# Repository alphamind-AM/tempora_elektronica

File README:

author: Alphamind
year: 2024
dyslexia: yes

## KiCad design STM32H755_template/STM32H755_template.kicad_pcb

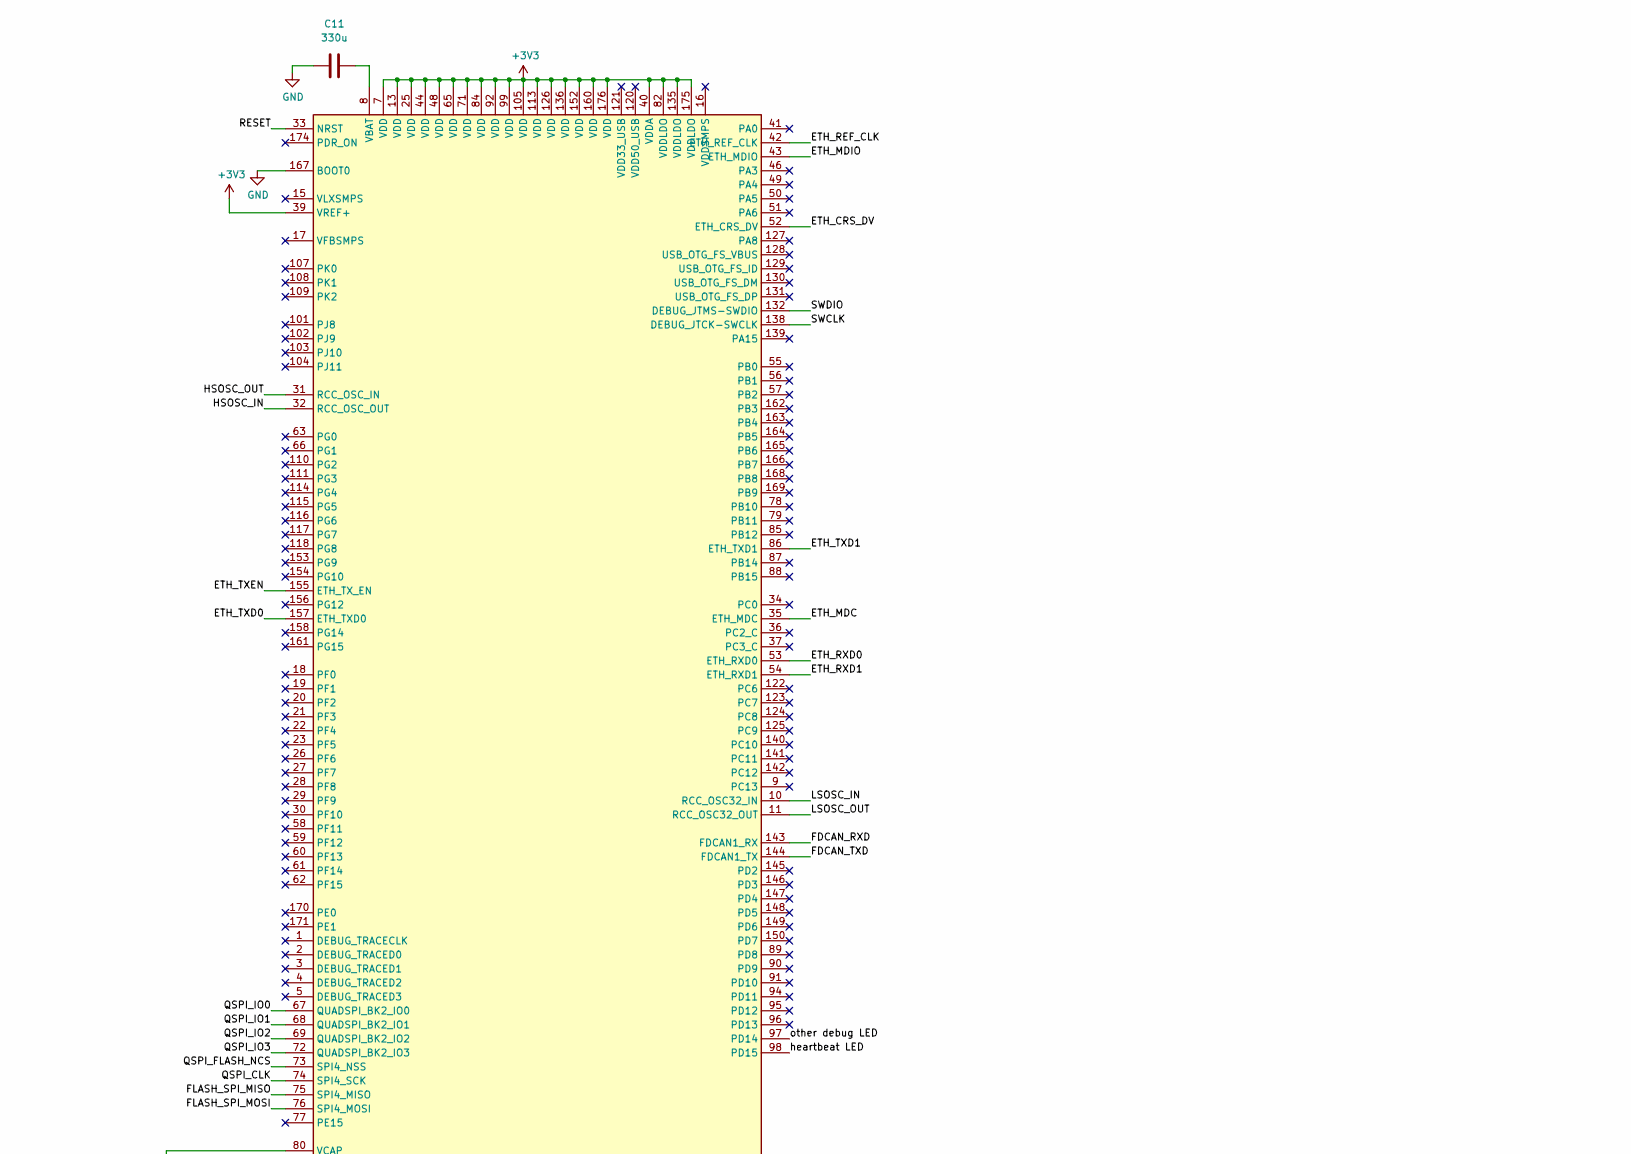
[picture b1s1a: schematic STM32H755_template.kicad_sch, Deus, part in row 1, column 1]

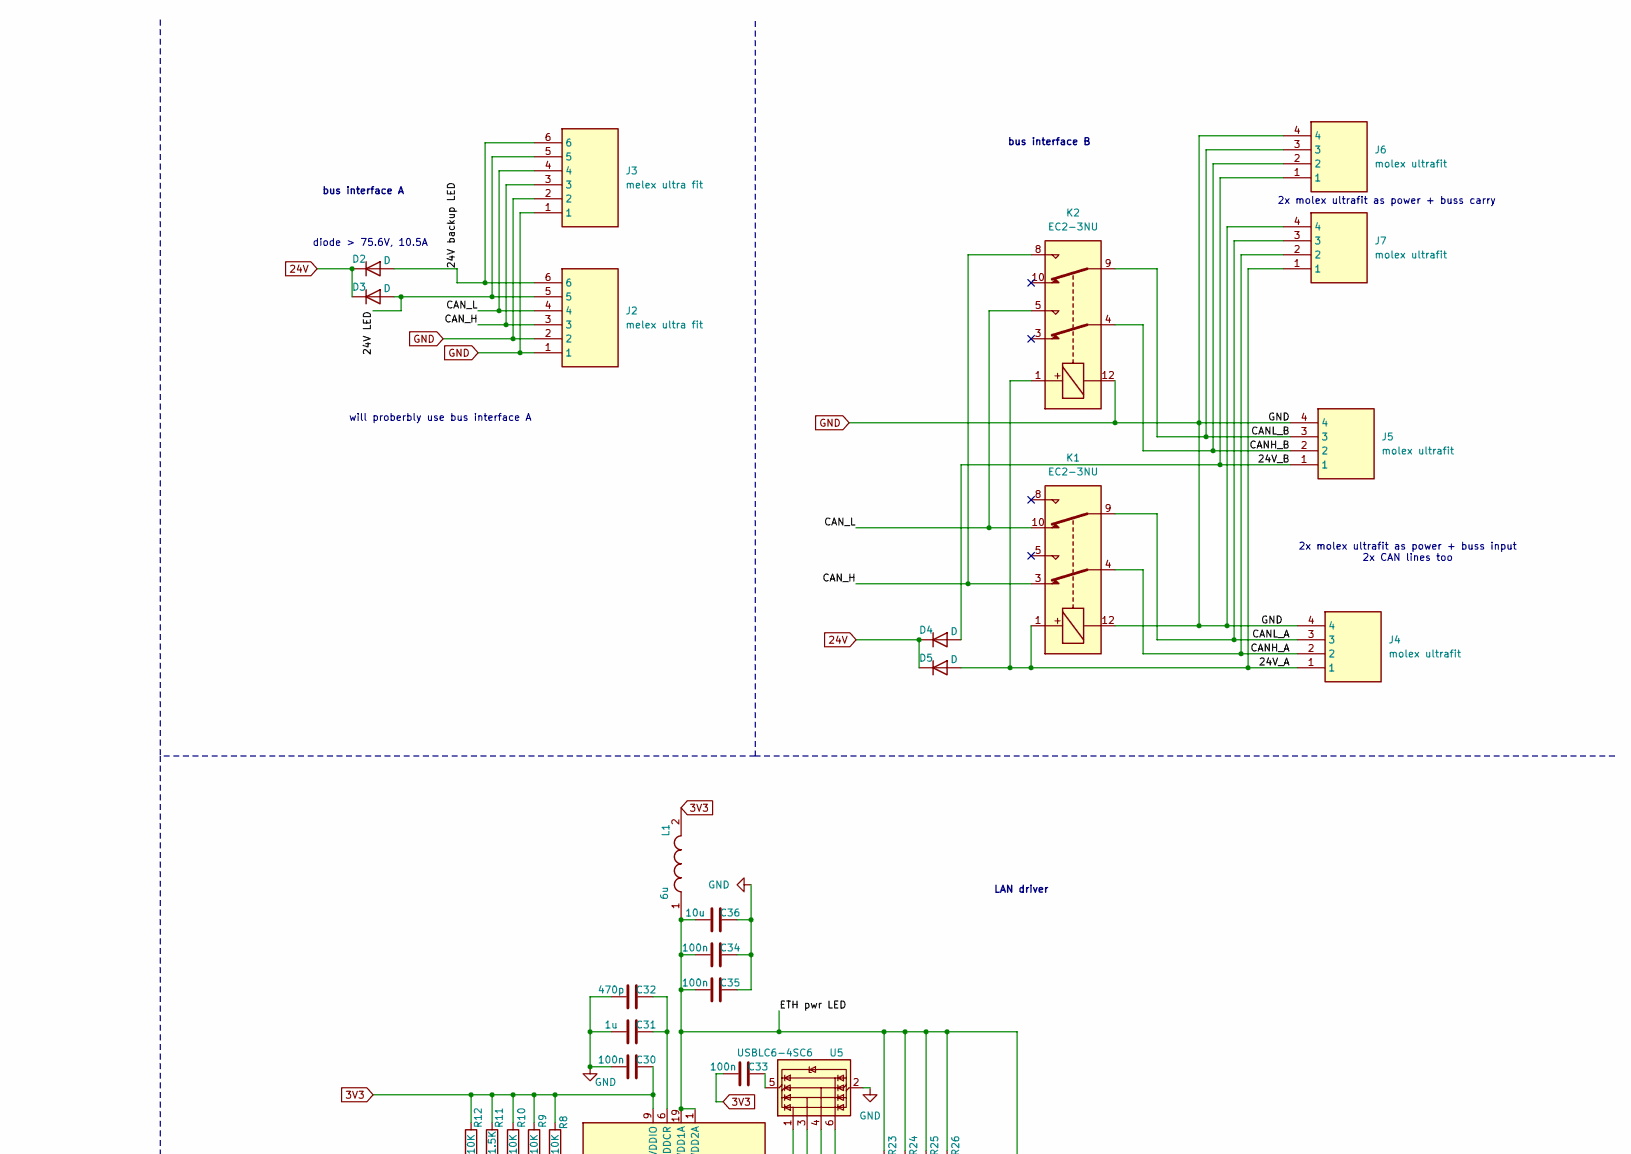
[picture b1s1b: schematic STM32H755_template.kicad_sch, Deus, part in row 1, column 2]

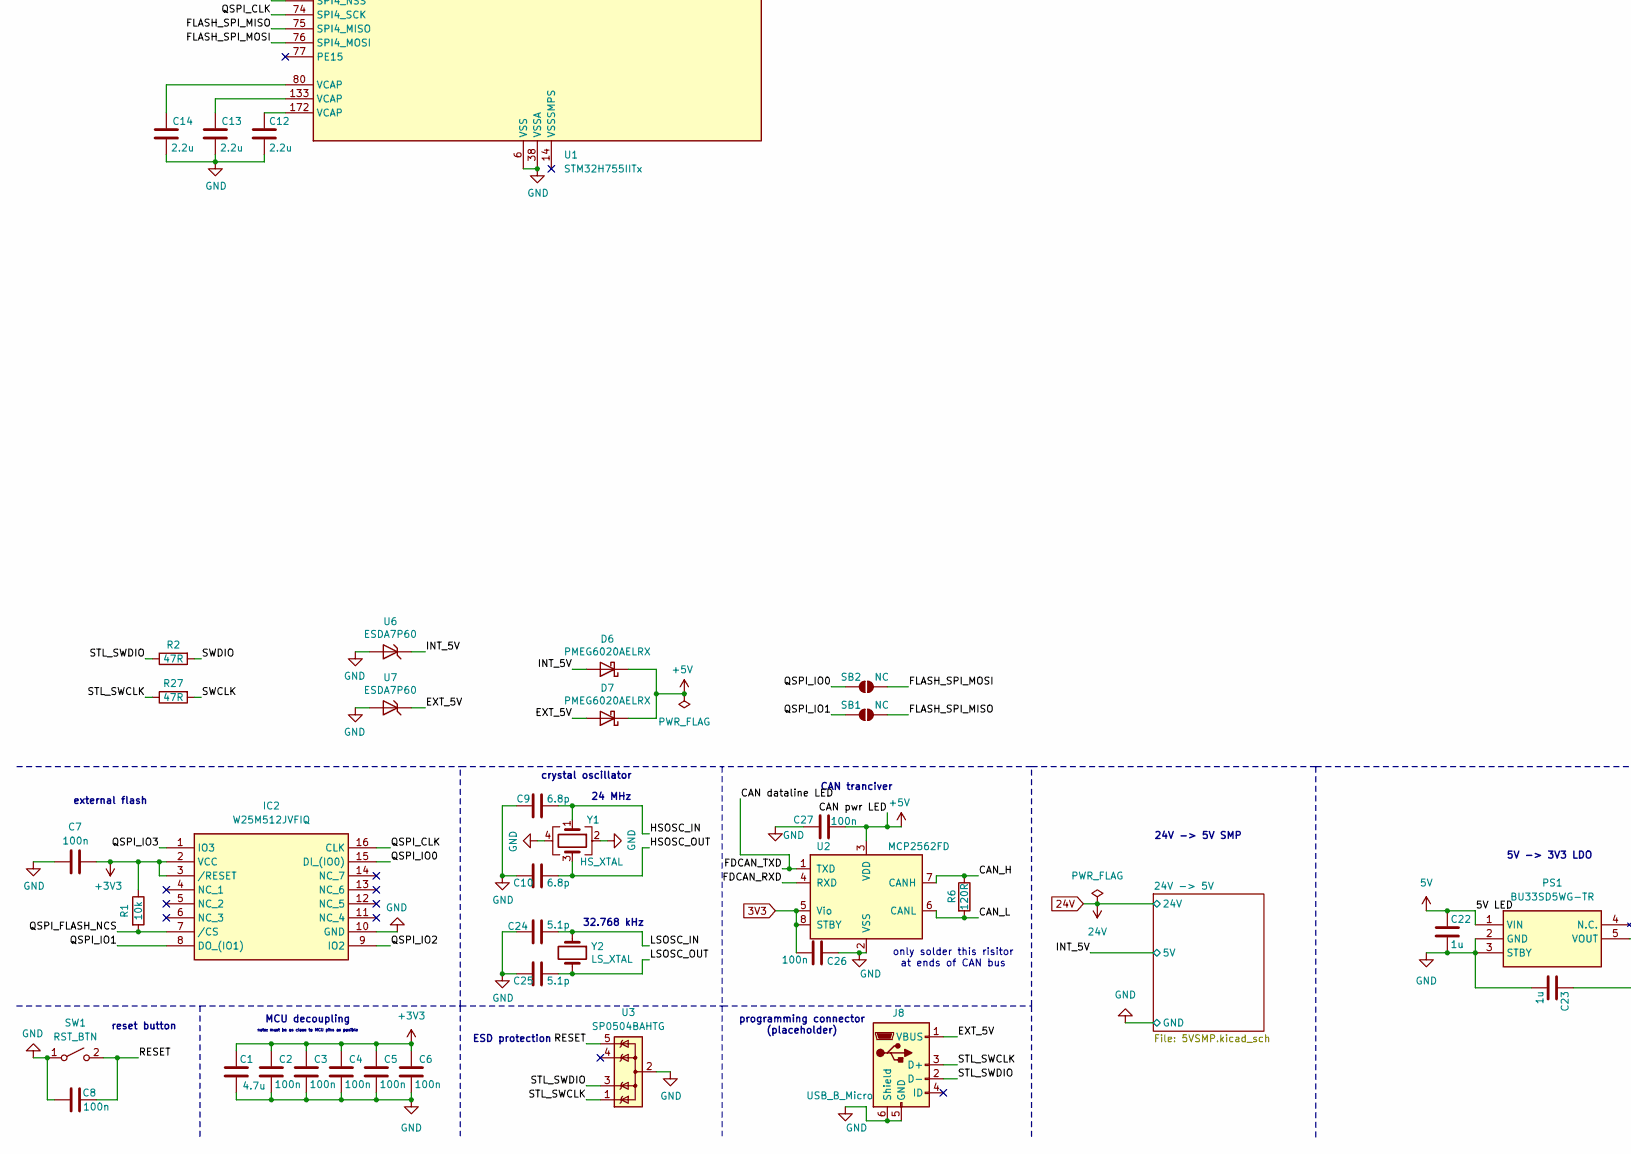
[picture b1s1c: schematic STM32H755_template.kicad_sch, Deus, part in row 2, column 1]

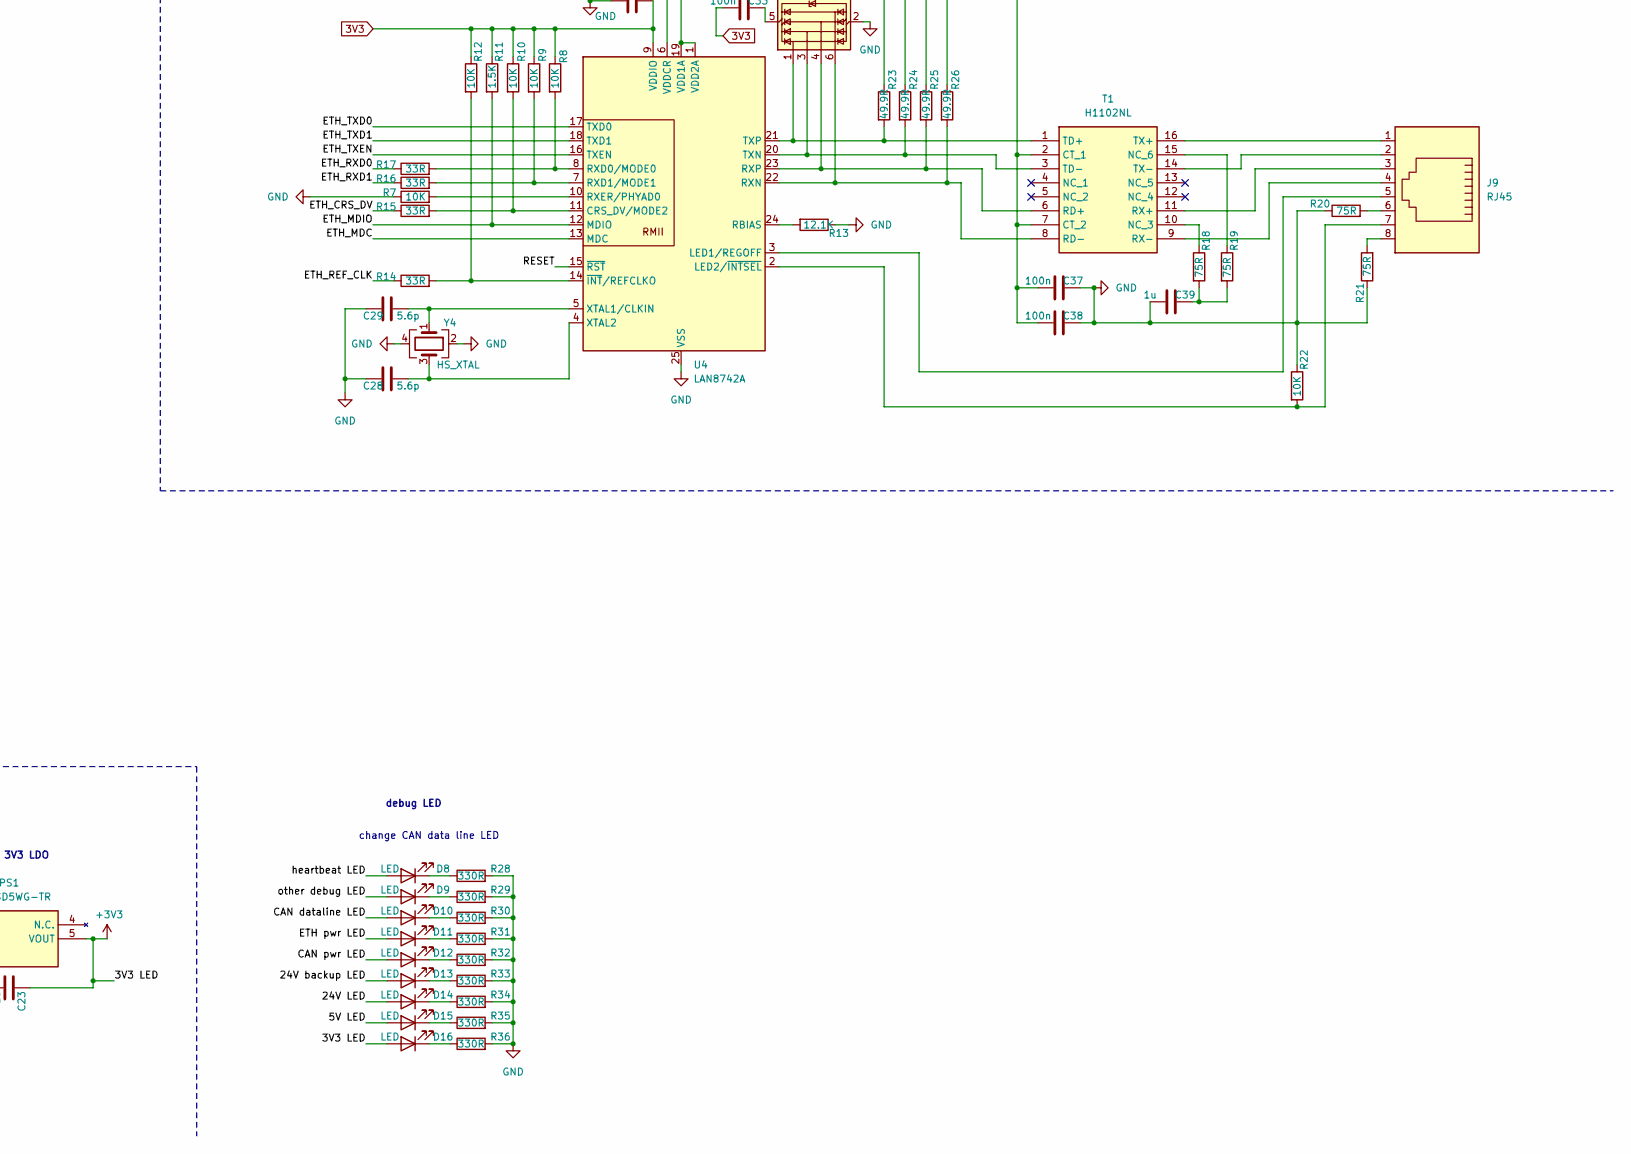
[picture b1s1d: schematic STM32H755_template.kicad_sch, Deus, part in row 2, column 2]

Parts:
C1: 4.7u; C_0603_1608Metric
C2, C3, C4, C5, C6, C26, C27: 100n; C_0603_1608Metric
C7, C8, C30, C33, C34, C35, C37, C38: 100n; C_0603_1608Metric_Pad1.08x0.95mm_HandSolder
C9, C10: 6.8p; C_0603_1608Metric_Pad1.08x0.95mm_HandSolder
C11: 330u; C_1206_3216Metric
C12, C13, C14: 2.2u; C_0603_1608Metric
C22, C23: 1u; C_0603_1608Metric
C24, C25: 5.1p; C_0603_1608Metric_Pad1.08x0.95mm_HandSolder
C28, C29: 5.6p; C_0603_1608Metric_Pad1.08x0.95mm_HandSolder
C31, C39: 1u; C_0603_1608Metric_Pad1.08x0.95mm_HandSolder
C32: 470p; C_0603_1608Metric_Pad1.08x0.95mm_HandSolder
C36: 10u; C_0603_1608Metric_Pad1.08x0.95mm_HandSolder
D2, D3, D4, D5: D; D_0603_1608Metric
D6, D7: PMEG6020AELRX; D_SOD-123
D8, D9, D10, D11, D12, D13, D14, D15, D16: LED; LED_0603_1608Metric
IC2: W25M512JVFIQ; SOIC127P1032X264-16N; Mouser Part Number 454-W25M512JVFIQ
J2, J3: melex ultra fit; Molex_Micro-Fit_3.0_43650-0600_1x06_P3.00mm_Horizontal; Mouser Part Number 538-43650-0600
J4, J5, J6, J7: molex ultrafit; Molex_Micro-Fit_3.0_43650-0400_1x04_P3.00mm_Horizontal; Mouser Part Number 538-43650-0400
J8: USB_B_Micro; USB_Micro-AB_Molex_47590-0001
J9: RJ45; RJ45_HALO_HFJ11-x2450ERL_Horizontal
K1, K2: EC2-3NU; Relay_DPDT_Kemet_EC2
L1: 6u; SRN6028C6R0M; Mouser Part Number 652-SRN6028C-6R0M
PS1: BU33SD5WG-TR; SOIC127P600X170-9N; Mouser Part Number 755-BU33SD5WG-TR
R1: 10k; R_0603_1608Metric_Pad0.98x0.95mm_HandSolder
R2, R27: 47R; R_0603_1608Metric_Pad0.98x0.95mm_HandSolder
R6: 120R; R_0603_1608Metric
R7, R8, R9, R10, R12, R22: 10K; R_0603_1608Metric
R11: 1.5K; R_0603_1608Metric
R13: 12.1K; R_0603_1608Metric
R14, R15, R16, R17: 33R; R_0603_1608Metric
R18, R19, R20, R21: 75R; R_0603_1608Metric
R23, R24, R25, R26: 49.9R; R_0603_1608Metric
R28, R29, R30, R31, R32, R33, R34, R35, R36: 330R; R_0603_1608Metric
SB1, SB2: NC; SolderJumper-2_P1.3mm_Open_TrianglePad1.0x1.5mm
SW1: RST_BTN; SW_SPST_EVQP7A
T1: H1102NL; SOIC127P940X597-16N; Mouser Part Number 673-H1102NL
U1: STM32H755IITx; LQFP-176_24x24mm_P0.5mm
U2: MCP2562FD; SOIC-8_3.9x4.9mm_P1.27mm
U3: SP0504BAHTG; SOT-23-5
U4: LAN8742A; VQFN-24-1EP_4x4mm_P0.5mm_EP2.45x2.45mm_ThermalVias
U5: USBLC6-4SC6; SOT-23-6
U6, U7: ESDA7P60; ST1610
Y1, Y4: HS_XTAL; Crystal_SMD_2016-4Pin_2.0x1.6mm
Y2: LS_XTAL; Crystal_SMD_3215-2Pin_3.2x1.5mm

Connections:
3V3: C26.2, C30.2, C33.1, L1.2, R8.1, R9.1, R10.1, R11.1, R12.1, U2.5 (Vio), U2.8 (STBY), U4.9 (VDDIO)
5V: C22.1, D15.2 (A), PS1.1 (VIN)
24V: D2.1 (K), D3.1 (K), D4.1 (K), D5.1 (K); also elsewhere on the board
+3V3: C1.1, C2.1, C3.1, C4.1, C5.1, C6.1, C7.1, C23.1, D16.2 (A), IC2.2 (VCC), IC2.3 (/RESET), PS1.5 (VOUT), R1.1, U1.7 (VDD), U1.13 (VDD), U1.25 (VDD), U1.39 (VREF+), U1.40 (VDDA), U1.44 (VDD), U1.48 (VDD), U1.65 (VDD), U1.71 (VDD), U1.82 (VDDLDO), U1.84 (VDD), U1.92 (VDD), U1.99 (VDD), U1.105 (VDD), U1.113 (VDD), U1.126 (VDD), U1.135 (VDDLDO), U1.136 (VDD), U1.152 (VDD), U1.160 (VDD), U1.175 (VDDLDO), U1.176 (VDD)
+5V: C27.2, D6.1 (K), D7.1 (K), D12.2 (A), U2.3 (VDD)
/24V LED: D3.2 (A), D14.2 (A), J2.5, J3.5
/24V backup LED: D2.2 (A), D13.2 (A), J2.6, J3.6
/24V_A: D5.2 (A), J4.1, J7.1, K1.1, K2.1
/24V_B: D4.2 (A), J5.1, J6.1
/CAN dataline LED: D10.2 (A), U1.144 (FDCAN1_TX), U2.1 (TXD)
/CANH_A: J4.2, J7.2, K1.4
/CANH_B: J5.2, J6.2, K2.4
/CANL_A: J4.3, J7.3, K1.9
/CANL_B: J5.3, J6.3, K2.9
/CAN_H: J2.3, J3.3, K1.3, K2.8, R6.1, U2.7 (CANH)
/CAN_L: J2.4, J3.4, K1.10, K2.5, R6.2, U2.6 (CANL)
/ETH pwr LED: C34.1, C35.1, C36.1, C37.1, C38.1, D11.2 (A), L1.1, R23.1, R24.1, R25.1, R26.1, T1.2 (CT_1), T1.7 (CT_2), U4.1 (VDD2A), U4.19 (VDD1A)
/ETH_CRS_DV: R15.1, U1.52 (ETH_CRS_DV)
/ETH_MDC: U1.35 (ETH_MDC), U4.13 (MDC)
/ETH_MDIO: R11.2, U1.43 (ETH_MDIO), U4.12 (MDIO)
/ETH_REF_CLK: R14.1, U1.42 (ETH_REF_CLK)
/ETH_RXD0: R17.1, U1.53 (ETH_RXD0)
/ETH_RXD1: R16.1, U1.54 (ETH_RXD1)
/ETH_TXD0: U1.157 (ETH_TXD0), U4.17 (TXD0)
/ETH_TXD1: U1.86 (ETH_TXD1), U4.18 (TXD1)
/ETH_TXEN: U1.155 (ETH_TX_EN), U4.16 (TXEN)
/EXT_5V: D7.2 (A), J8.1 (VBUS), U7.1 (A1)
/FDCAN_RXD: U1.143 (FDCAN1_RX), U2.4 (RXD)
/FLASH_SPI_MISO: SB1.2 (B), U1.75 (SPI4_MISO)
/FLASH_SPI_MOSI: SB2.2 (B), U1.76 (SPI4_MOSI)
/HSOSC_IN: C9.2, U1.32 (RCC_OSC_OUT), Y1.1
/HSOSC_OUT: C10.1, U1.31 (RCC_OSC_IN), Y1.3
/INT_5V: D6.2 (A), U6.1 (A1); also elsewhere on the board
/LSOSC_IN: C24.2, U1.10 (RCC_OSC32_IN), Y2.1
/LSOSC_OUT: C25.1, U1.11 (RCC_OSC32_OUT), Y2.2
/QSPI_CLK: IC2.16 (CLK), U1.74 (SPI4_SCK)
/QSPI_FLASH_NCS: IC2.7 (/CS), R1.2, U1.73 (SPI4_NSS)
/QSPI_IO0: IC2.15 (DI_(IO0)), SB2.1 (A), U1.67 (QUADSPI_BK2_IO0)
/QSPI_IO1: IC2.8 (DO_(IO1)), SB1.1 (A), U1.68 (QUADSPI_BK2_IO1)
/QSPI_IO2: IC2.9 (IO2), U1.69 (QUADSPI_BK2_IO2)
/QSPI_IO3: IC2.1 (IO3), U1.72 (QUADSPI_BK2_IO3)
/RESET: C8.1, SW1.2 (B), U1.33 (NRST), U3.5 (IO4), U4.15 (~RST)
/STL_SWCLK: J8.3 (D+), R27.1, U3.1 (IO1)
/STL_SWDIO: J8.2 (D-), R2.1, U3.3 (IO2)
/SWCLK: R27.2, U1.138 (DEBUG_JTCK-SWCLK)
/SWDIO: R2.2, U1.132 (DEBUG_JTMS-SWDIO)
/heartbeat LED: D8.2 (A), U1.98 (PD15)
/other debug LED: D9.2 (A), U1.97 (PD14)
GND: C1.2, C2.2, C3.2, C4.2, C5.2, C6.2, C7.2, C8.2, C9.1, C10.2, C11.1, C12.2, C13.2, C14.2, C22.2, C23.2, C24.1, C25.2, C26.1, C27.1, C28.2, C29.2, C30.1, C31.1, C32.1, C34.2, C35.2, C36.2, C37.2, C38.2, C39.1, IC2.10 (GND), J2.1, J2.2, J3.1, J3.2, J4.4, J5.4, J6.4, J7.4, J8.5 (GND), J8.6 (Shield), K1.12, K2.12, PS1.2 (GND), PS1.3 (STBY), R7.1, R13.1, R20.1, R21.1, R22.1, R28.2, R29.2, R30.2, R31.2, R32.2, R33.2, R34.2, R35.2, R36.2, SW1.1 (A), U1.6 (VSS), U1.12 (VSS), U1.24 (VSS), U1.38 (VSSA), U1.45 (VSS), U1.47 (VSS), U1.64 (VSS), U1.70 (VSS), U1.81 (VSS), U1.83 (VSS), U1.93 (VSS), U1.100 (VSS), U1.106 (VSS), U1.112 (VSS), U1.119 (VSS), U1.134 (VSS), U1.137 (VSS), U1.151 (VSS), U1.159 (VSS), U1.167 (BOOT0), U1.173 (VSS), U2.2 (VSS), U3.2 (GND), U4.25 (VSS), U5.2 (GND), U6.2 (A2), U7.2 (A2), Y1.2, Y1.4, Y4.2, Y4.4; also elsewhere on the board
unnamed: C12.1, U1.172 (VCAP)
unnamed: C13.1, U1.133 (VCAP)
unnamed: C14.1, U1.80 (VCAP)
unnamed: C39.2, R18.2, R19.2
unnamed: D8.1 (K), R28.1
unnamed: D9.1 (K), R29.1
unnamed: D10.1 (K), R30.1
unnamed: D11.1 (K), R31.1
unnamed: D12.1 (K), R32.1
unnamed: D13.1 (K), R33.1
unnamed: D14.1 (K), R34.1
unnamed: D15.1 (K), R35.1
unnamed: D16.1 (K), R36.1
unnamed: J9.6, R20.2
unnamed: J9.8, R21.2
unnamed: R18.1, T1.10 (NC_3)
unnamed: R19.1, T1.15 (NC_6)
unnamed: R25.2, T1.6 (RD+), U4.23 (RXP), U5.4 (I/O3)
unnamed: R26.2, T1.8 (RD-), U4.22 (RXN), U5.6 (I/O4)
unnamed: J9.3, T1.11 (RX+)
unnamed: J9.4, T1.9 (RX-)
unnamed: R23.2, T1.1 (TD+), U4.21 (TXP), U5.1 (I/O1)
unnamed: R24.2, T1.3 (TD-), U4.20 (TXN), U5.3 (I/O2)
unnamed: J9.1, T1.16 (TX+)
unnamed: J9.2, T1.14 (TX-)
unnamed: C11.2, U1.8 (VBAT)
unnamed: R10.2, R15.2, U4.11 (CRS_DV/MODE2)
unnamed: J9.5, U4.3 (LED1/REGOFF)
unnamed: J9.7, R22.2, U4.2 (LED2/~INTSEL)
unnamed: R13.2, U4.24 (RBIAS)
unnamed: R8.2, R17.2, U4.8 (RXD0/MODE0)
unnamed: R9.2, R16.2, U4.7 (RXD1/MODE1)
unnamed: R7.2, U4.10 (RXER/PHYAD0)
unnamed: C31.2, C32.2, U4.6 (VDDCR)
unnamed: C29.1, U4.5 (XTAL1/CLKIN), Y4.1
unnamed: C28.1, U4.4 (XTAL2), Y4.3
unnamed: R12.2, R14.2, U4.14 (~INT/REFCLKO)
unnamed: C33.2, U5.5 (VBUS)

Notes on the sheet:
24 MHz
32.768 kHz
bus interface A
crystal oscillator
diode > 75.6V, 10.5A
debug LED
programming connector (placeholder)
bus interface B
24V -> 5V SMP
reset button
5V -> 3V3 LDO
ESD protection
external flash
CAN tranciver
note: must be as close to MCU pins as posible
will proberbly use bus interface A
LAN driver
MCU decoupling
2x molex ultrafit as power + buss carry
only solder this risitor at ends of CAN bus
2x molex ultrafit as power + buss input 2x CAN lines too
change CAN data line LED

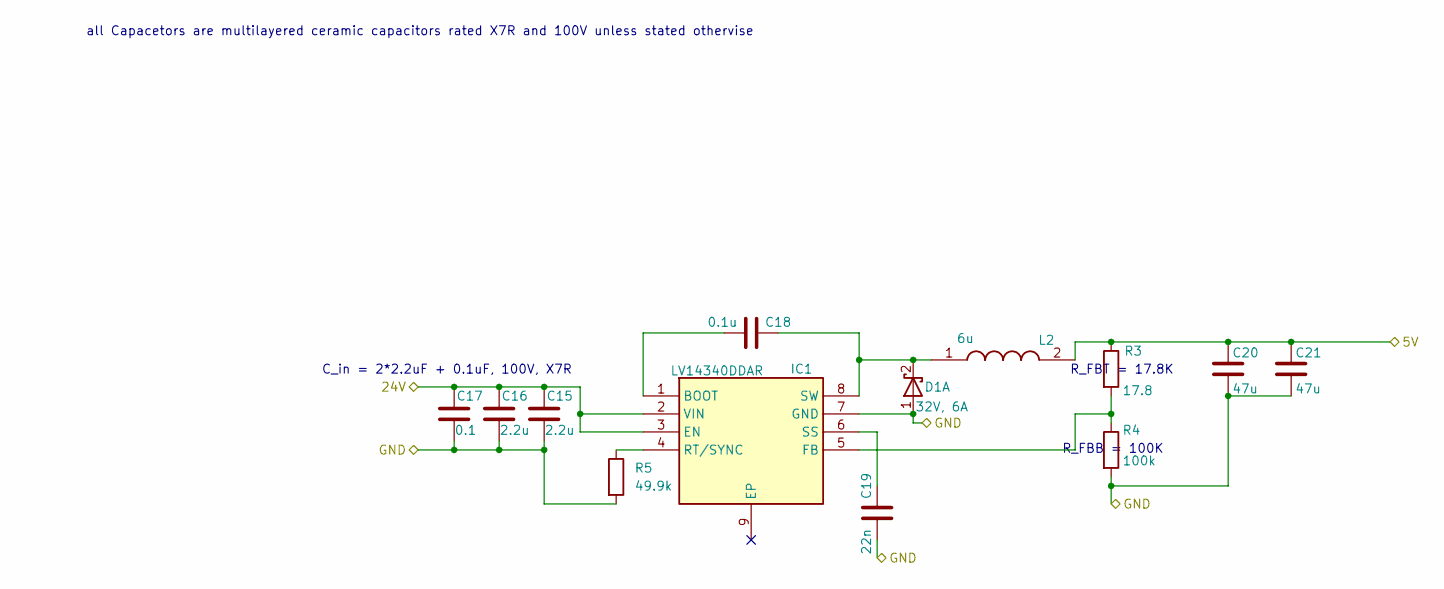
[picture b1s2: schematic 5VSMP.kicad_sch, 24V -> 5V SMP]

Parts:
C15, C16: 2.2u; C_0603_1608Metric
C17: 0.1; C_0603_1608Metric
C18: 0.1u; C_0603_1608Metric
C19: 22n; C_0603_1608Metric
C20, C21: 47u; C_0603_1608Metric
D1: 32V, 6A; D_0603_1608Metric
IC1: LV14340DDAR; SOIC127P600X170-9N; Mouser Part Number 595-LV14340DDAR
L2: 6u; SRN6028C6R0M; Mouser Part Number 652-SRN6028C-6R0M
R3: 17.8; R_0603_1608Metric
R4: 100k; R_0603_1608Metric
R5: 49.9k; R_0603_1608Metric

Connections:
24V: C15.1, C16.1, C17.1, IC1.2 (VIN), IC1.3 (EN); also elsewhere on the board
/INT_5V: C20.1, C21.1, L2.2, R3.1; also elsewhere on the board
GND: C15.2, C16.2, C17.2, C19.1, C20.2, C21.2, D1.1 (A), IC1.7 (GND), R4.2, R5.2; also elsewhere on the board
unnamed: C18.2, D1.2 (K), IC1.8 (SW), L2.1
unnamed: C18.1, IC1.1 (BOOT)
unnamed: IC1.5 (FB), R3.2, R4.1
unnamed: IC1.4 (RT/SYNC), R5.1
unnamed: C19.2, IC1.6 (SS)

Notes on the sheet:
R_FBT = 17.8K
R_FBB = 100K
C_in = 2*2.2uF + 0.1uF, 100V, X7R
all Capacetors are multilayered ceramic capacitors rated X7R and 100V unless stated othervise

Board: 2 copper layers, 112 parts (0 on the bottom side), 80 nets, no tracks yet.

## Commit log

2024-09-05 more LEDS
